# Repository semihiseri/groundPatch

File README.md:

# groundPatch
Tired of being zapped? Try ground patch!

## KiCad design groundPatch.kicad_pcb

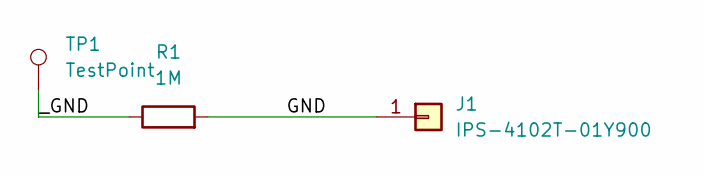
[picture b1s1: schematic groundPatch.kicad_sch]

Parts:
J1: IPS-4102T-01Y900
R1: 1M; R_1206_3216Metric_Pad1.30x1.75mm_HandSolder
TP1: TestPoint; GroundLogo

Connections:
/GND: J1.1, R1.2
/_GND: R1.1, TP1.1

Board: 2 copper layers, 3 parts (2 on the bottom side), 2 nets, no tracks yet.

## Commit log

2022-09-27 Initial design, fully ready
